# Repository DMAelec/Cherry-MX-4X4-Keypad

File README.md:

# Cherry MX 4X4 Keypad
A simple 16 key mechanical keypad designed for use with microcontrollers. This keypad is similar to the membrane 
ones used in Arduino projects but instead using Cherry MX switches with backlighting. You can use interface this
with Arduinos or Raspberry Pi, or even use it on a more advanced microcontroller like the teensy or the pro micro 
and load up QMK for a custom macropad.
 
Completely through hole PCB with provisions for 3mm LED backlighting and for NKRO diodes. Designed with Kicad 5.1 and 
files include schematic and drill template for mounting holes.

NOTE: If using NKRO diodes some Arduino sketches won't register keys unless you modify the code or insert the diodes backwards.

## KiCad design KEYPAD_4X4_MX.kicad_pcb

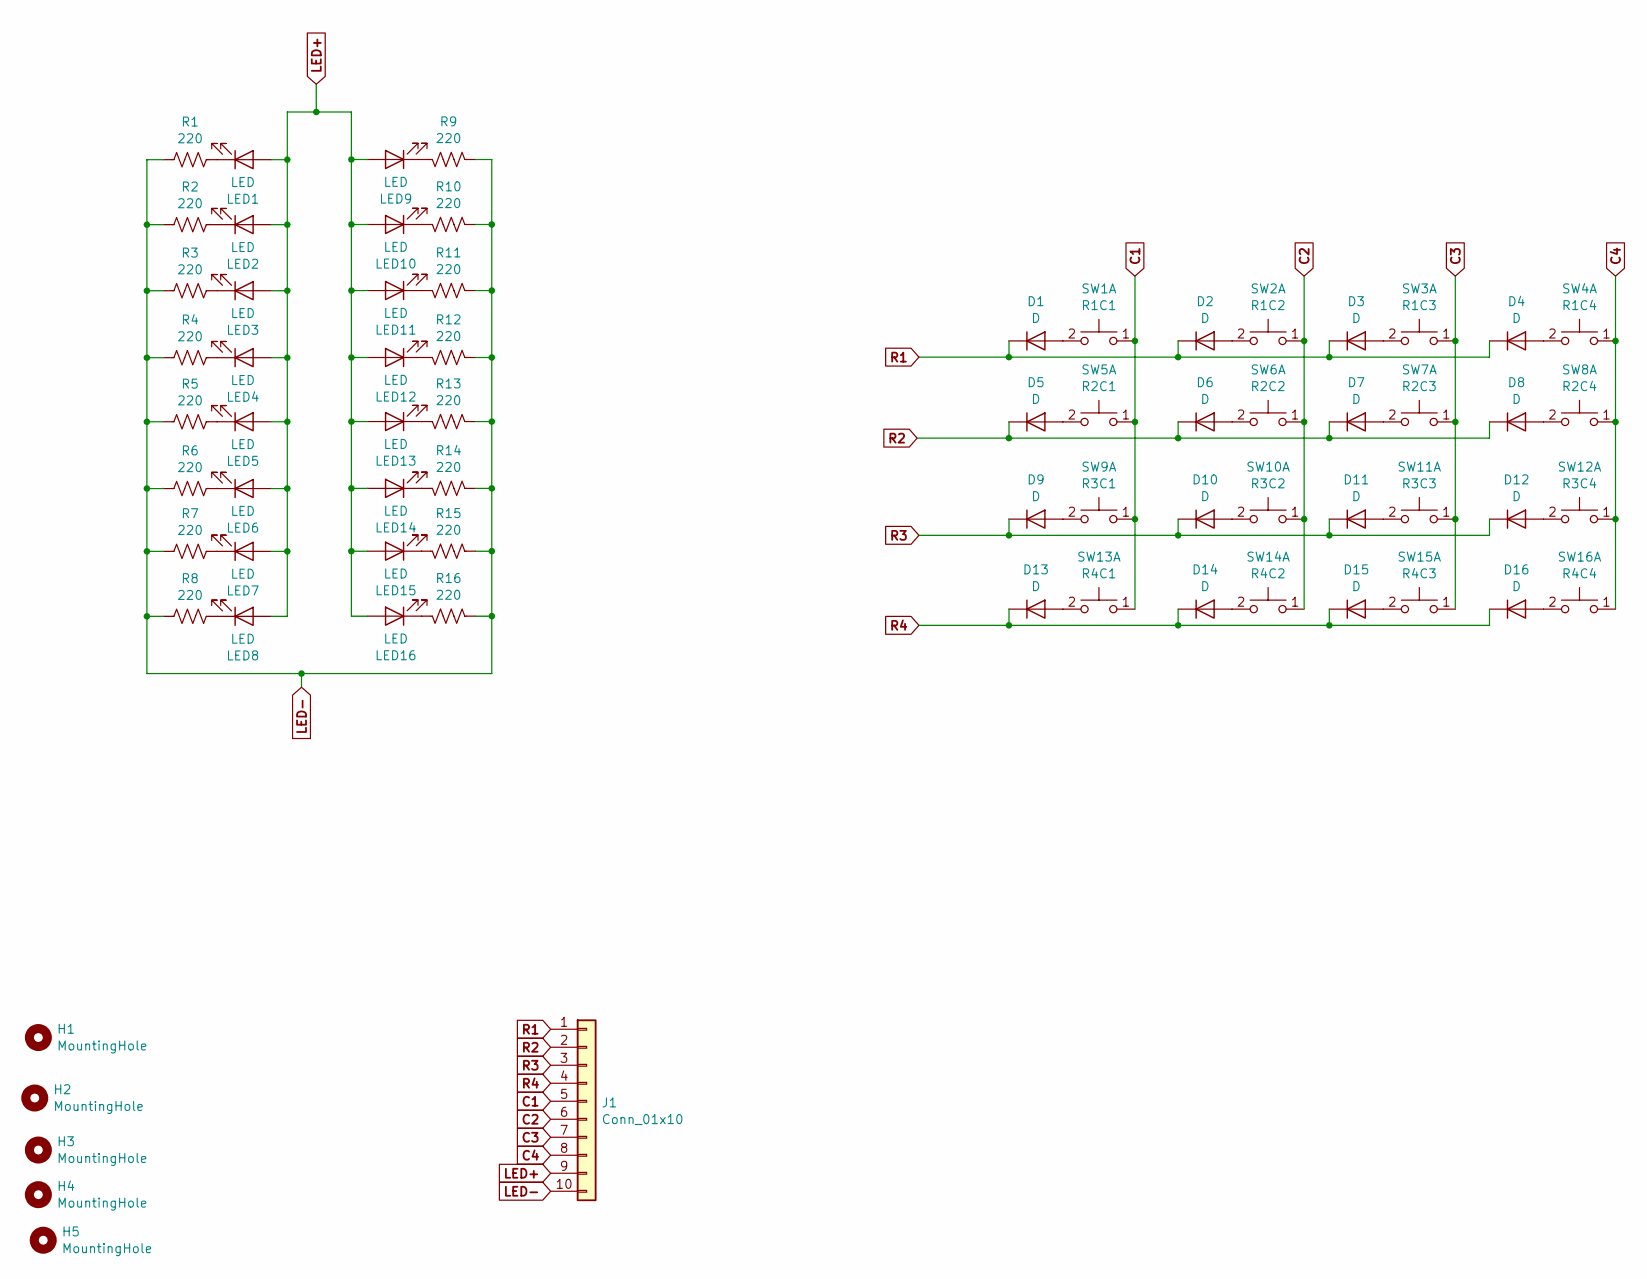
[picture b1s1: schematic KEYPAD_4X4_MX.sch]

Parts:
D1, D2, D3, D4, D5, D6, D7, D8, D9, D10, D11, D12, D13, D14, D15, D16: D; D_DO-35_SOD27_P7.62mm_Horizontal
H1, H2, H3, H4, H5: MountingHole; MountingHole_3.2mm_M3
J1: Conn_01x10; PinHeader_1x10_P2.54mm_Vertical
LED1, LED2, LED3, LED4, LED5, LED6, LED7, LED8, LED9, LED10, LED11, LED12, LED13, LED14, LED15, LED16: LED; LED_D3.0mm
R1, R2, R3, R4, R5, R6, R7, R8, R9, R10, R11, R12, R13, R14, R15, R16: 220; R_Axial_DIN0207_L6.3mm_D2.5mm_P7.62mm_Horizontal
SW1: R1C1; SW_Cherry_MX1A_1.00u_PCB
SW2: R1C2; SW_Cherry_MX1A_1.00u_PCB
SW3: R1C3; SW_Cherry_MX1A_1.00u_PCB
SW4: R1C4; SW_Cherry_MX1A_1.00u_PCB
SW5: R2C1; SW_Cherry_MX1A_1.00u_PCB
SW6: R2C2; SW_Cherry_MX1A_1.00u_PCB
SW7: R2C3; SW_Cherry_MX1A_1.00u_PCB
SW8: R2C4; SW_Cherry_MX1A_1.00u_PCB
SW9: R3C1; SW_Cherry_MX1A_1.00u_PCB
SW10: R3C2; SW_Cherry_MX1A_1.00u_PCB
SW11: R3C3; SW_Cherry_MX1A_1.00u_PCB
SW12: R3C4; SW_Cherry_MX1A_1.00u_PCB
SW13: R4C1; SW_Cherry_MX1A_1.00u_PCB
SW14: R4C2; SW_Cherry_MX1A_1.00u_PCB
SW15: R4C3; SW_Cherry_MX1A_1.00u_PCB
SW16: R4C4; SW_Cherry_MX1A_1.00u_PCB

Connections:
C1: J1.5, SW1.1 (C), SW5.1 (C), SW9.1 (C), SW13.1 (C)
C2: J1.6, SW2.1 (C), SW6.1 (C), SW10.1 (C), SW14.1 (C)
C3: J1.7, SW3.1 (C), SW7.1 (C), SW11.1 (C), SW15.1 (C)
C4: J1.8, SW4.1 (C), SW8.1 (C), SW12.1 (C), SW16.1 (C)
LED+: J1.9, LED1.2 (A), LED2.2 (A), LED3.2 (A), LED4.2 (A), LED5.2 (A), LED6.2 (A), LED7.2 (A), LED8.2 (A), LED9.2 (A), LED10.2 (A), LED11.2 (A), LED12.2 (A), LED13.2 (A), LED14.2 (A), LED15.2 (A), LED16.2 (A)
LED-: J1.10, R1.2, R2.2, R3.2, R4.2, R5.2, R6.2, R7.2, R8.2, R9.2, R10.2, R11.2, R12.2, R13.2, R14.2, R15.2, R16.2
unnamed: D1.2 (A), SW1.2 (D)
unnamed: D2.2 (A), SW2.2 (D)
unnamed: D3.2 (A), SW3.2 (D)
unnamed: D4.2 (A), SW4.2 (D)
unnamed: D5.2 (A), SW5.2 (D)
unnamed: D6.2 (A), SW6.2 (D)
unnamed: D7.2 (A), SW7.2 (D)
unnamed: D8.2 (A), SW8.2 (D)
unnamed: D9.2 (A), SW9.2 (D)
unnamed: D10.2 (A), SW10.2 (D)
unnamed: D11.2 (A), SW11.2 (D)
unnamed: D12.2 (A), SW12.2 (D)
unnamed: D13.2 (A), SW13.2 (D)
unnamed: D14.2 (A), SW14.2 (D)
unnamed: D15.2 (A), SW15.2 (D)
unnamed: D16.2 (A), SW16.2 (D)
unnamed: LED1.1 (K), R1.1
unnamed: LED2.1 (K), R2.1
unnamed: LED3.1 (K), R3.1
unnamed: LED4.1 (K), R4.1
unnamed: LED5.1 (K), R5.1
unnamed: LED6.1 (K), R6.1
unnamed: LED7.1 (K), R7.1
unnamed: LED8.1 (K), R8.1
unnamed: LED9.1 (K), R9.1
unnamed: LED10.1 (K), R10.1
unnamed: LED11.1 (K), R11.1
unnamed: LED12.1 (K), R12.1
unnamed: LED13.1 (K), R13.1
unnamed: LED14.1 (K), R14.1
unnamed: LED15.1 (K), R15.1
unnamed: LED16.1 (K), R16.1
R1: D1.1 (K), D2.1 (K), D3.1 (K), D4.1 (K), J1.1
R2: D5.1 (K), D6.1 (K), D7.1 (K), D8.1 (K), J1.2
R3: D9.1 (K), D10.1 (K), D11.1 (K), D12.1 (K), J1.3
R4: D13.1 (K), D14.1 (K), D15.1 (K), D16.1 (K), J1.4

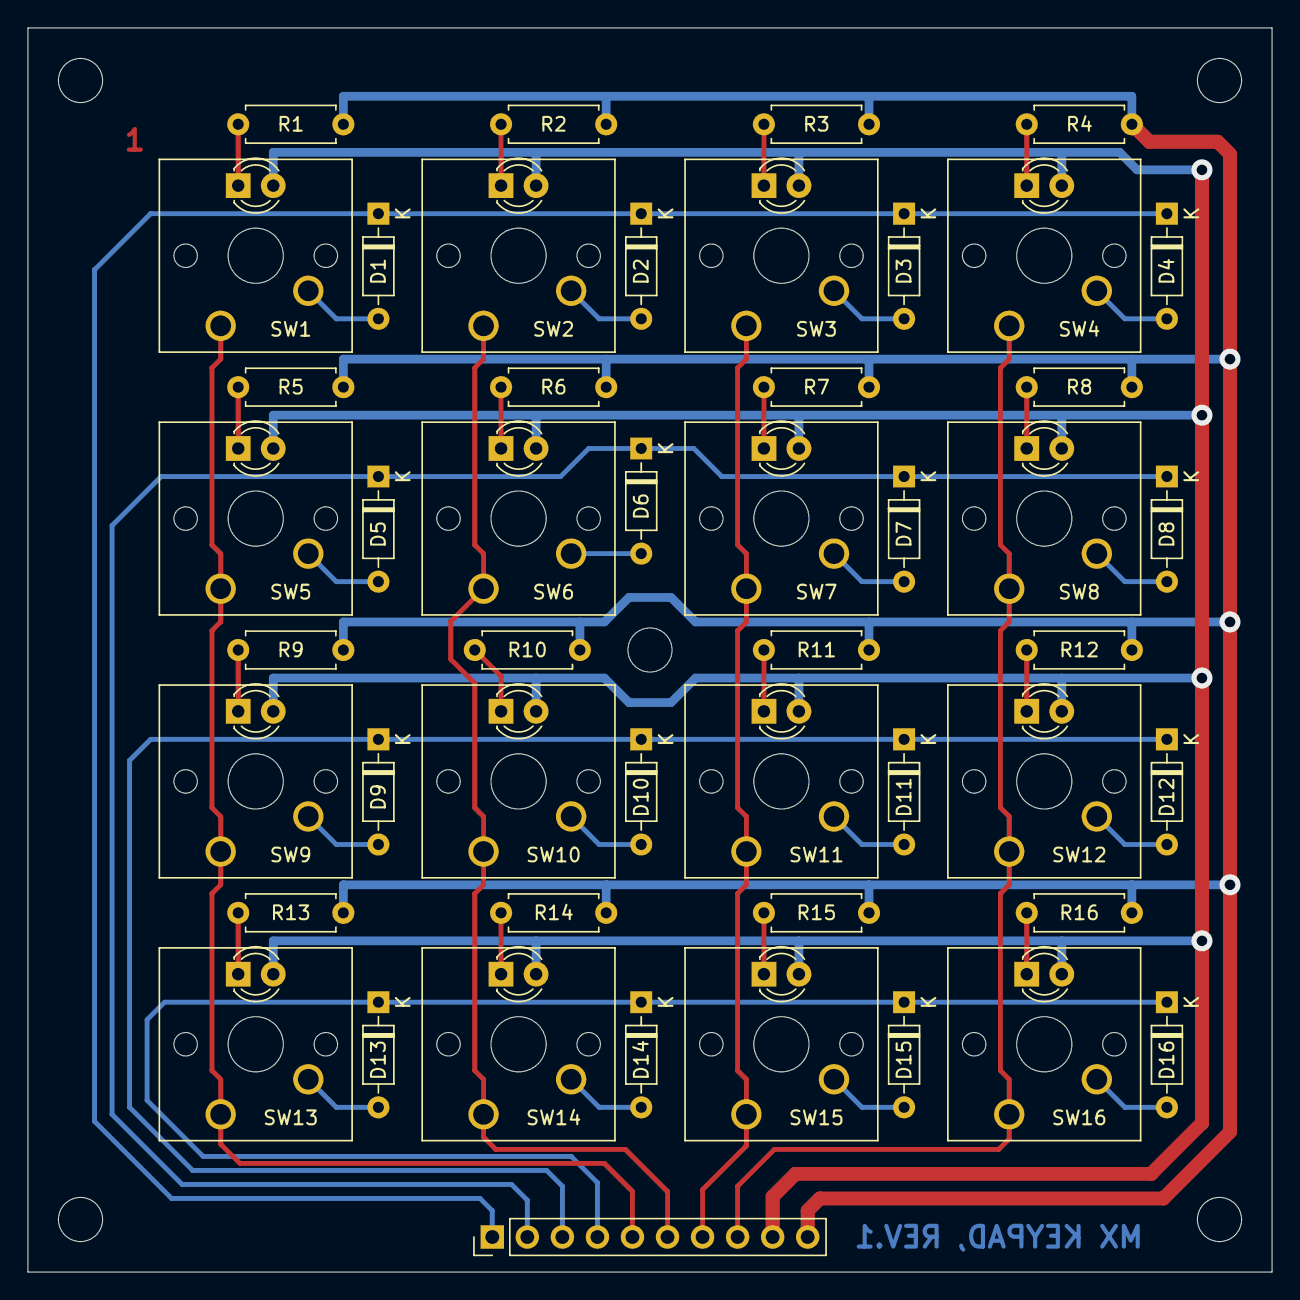
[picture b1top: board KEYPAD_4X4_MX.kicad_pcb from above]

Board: 2 copper layers, 90.2 x 90.2 mm, 70 parts (0 on the bottom side), 42 nets.

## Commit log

2023-01-19 Cleaned up Files
